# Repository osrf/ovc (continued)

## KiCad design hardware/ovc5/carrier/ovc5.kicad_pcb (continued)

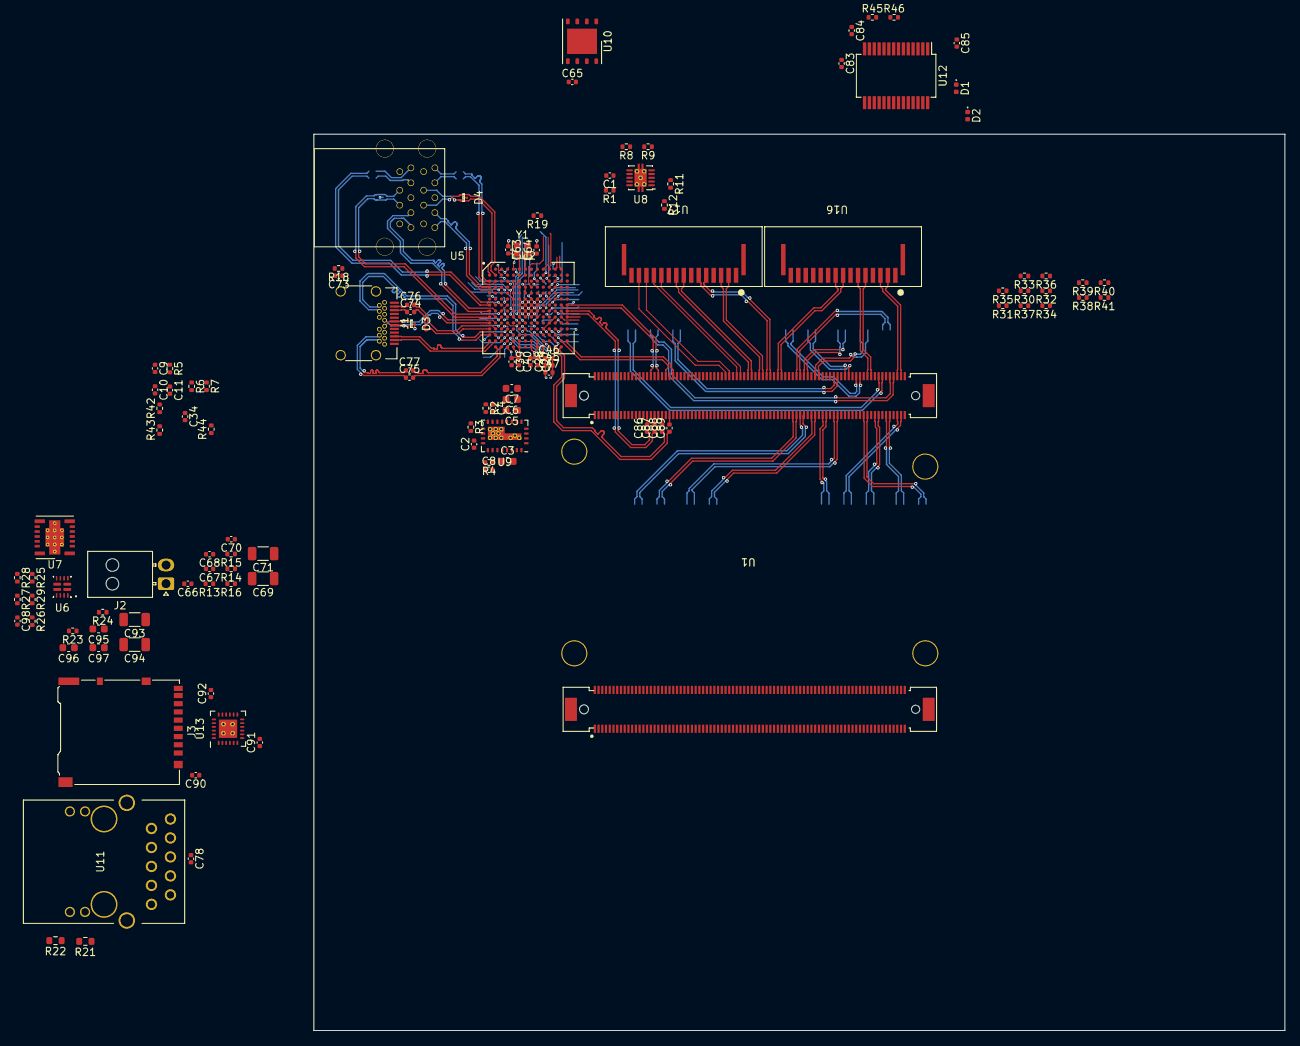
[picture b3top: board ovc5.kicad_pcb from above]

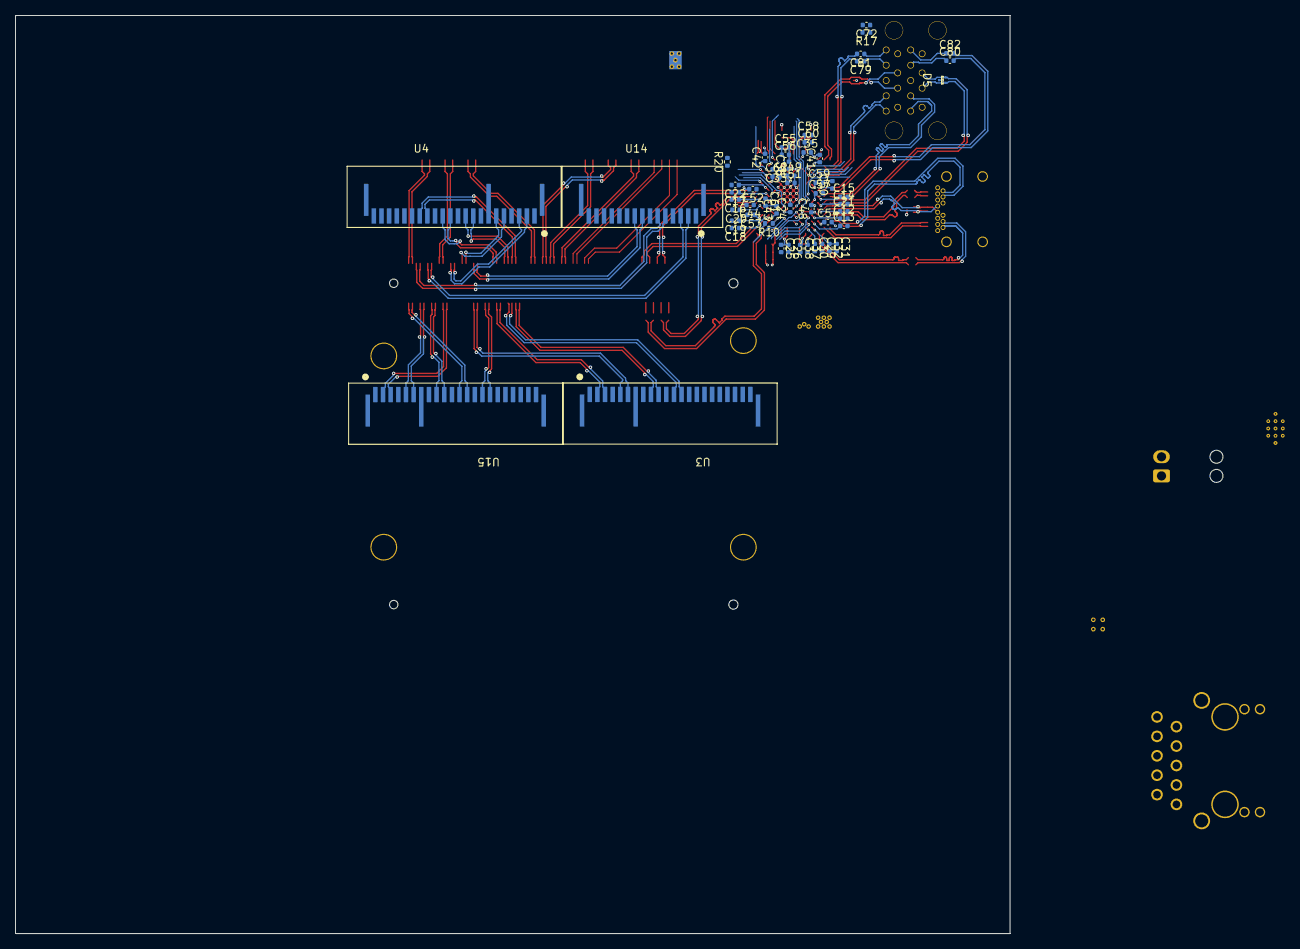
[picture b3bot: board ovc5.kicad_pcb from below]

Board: 6 copper layers, 130.0 x 120.0 mm, 169 parts (55 on the bottom side), 204 nets.

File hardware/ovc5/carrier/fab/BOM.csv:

Reference,Value,Footprint,D1N,D1PN,MFN,MPN,Quantity
"C25, C34, C47",10u,Capacitor_SMD:C_0402_1005Metric,Digikey,1276-6830-1-ND,Samsung,CL05A106MP8NUB8,3
"C2, C9, C33, C35, C55, C58, C90",1u,Capacitor_SMD:C_0402_1005Metric,Digikey,1276-1076-1-ND,Samsung,CL05A105KP5NNNC,7
"C1, C8, C10-C22, C24, C30, C32, C36-C45, C48-C50, C52-C54, C56, C57, C59-C61, C65-C68, C70, C74-C89, C91, C92, C98-C101",100n,Capacitor_SMD:C_0402_1005Metric,Digikey,1276-1043-1-ND,Samsung,CL05A104KA5NNNC,66
"C26-C28, C46, C51",10n,Capacitor_SMD:C_0402_1005Metric,Digikey,1276-1051-1-ND,Samsung,CL05B103KO5NNNC,5
"C29, C31, C62",4u7,Capacitor_SMD:C_0402_1005Metric,Digikey,587-3408-1-ND,Taiyo Yuden,LMK105BBJ475MVLF,3
"C4, C63, C64",10p,Capacitor_SMD:C_0402_1005Metric,Digikey,587-1947-1-ND,Taiyo Yuden,UMK105CG100DV-F,3
"C69, C71",150u,Capacitor_SMD:C_Elec_6.3x7.7,Digikey,PCE4401CT-ND,TDK,EEE-FKC151XAP,2
"C3, C5-C7, C23, C72, C73, C95-C97",22u,Capacitor_SMD:C_0603_1608Metric,Digikey,1276-6504-1-ND,Samsung,CL10A226MPCNUBE,10
"C93, C94",10u,Capacitor_SMD:C_1206_3216Metric,Digikey,1276-2876-1-ND,Samsung,CL31A106KBHNNNE,2
"C102, C103",2n2,Capacitor_SMD:C_0402_1005Metric,Digikey,1276-1532-1-ND,Samsung,CL05B222JB5NNNC,2
"CONN1, CONN2",Conn_Dummy,,Digikey,H122323-ND,Hirose,FX10A-168P-SV(71),2
D3-D5,D_TVS_Dual_AAC,USB:TPD2EUSB30x,Digikey,296-25509-1-ND,TI,TPD2EUSB30DRTR,3
"D2, D6",LED_Small,LED_SMD:LED_0402_1005Metric,Digikey,475-3112-1-ND,OSRAM,LB QH9G-N1OO-35-1,2
D7,LED_Small,LED_SMD:LED_0402_1005Metric,Digikey,475-3429-1-ND,OSRAM,LR VH9F-P2R1-1-Z,1
"D1, D8",LED_Small,LED_SMD:LED_0402_1005Metric,Digikey,475-3445-1-ND,OSRAM,LT VH9G-Q2OO-25-1,2
"FB1, FB2",MH2029-100Y,Inductor_SMD:L_0805_2012Metric,Digikey,MH2029-100YCT-ND,Bourns,MH2029-100Y,2
J1,USB_C_Receptacle,USB:USB_C_Receptacle_Wurth_632723300011,Digikey,732-9618-1-ND,Wurth,632723300011,1
J2,AUX_PWR,Connector_BarrelJack:BarrelJack_CUI_PJ-102AH_Horizontal,Digikey,CP-102AH-ND,CUI Devices,PJ-102AH,1
J3,Micro_SD_Card_Det_Hirose_DM3AT,Connector_Card:microSD_HC_Hirose_DM3AT-SF-PEJM5,RS-Online,828-1884,Hirose,DM3AT-SF-PEJM5,1
J4,JTAG,Connector_PinHeader_2.54mm:PinHeader_2x03_P2.54mm_Vertical,Digikey,1849-PR20203VBDN-ND,METZ Connect,PR20203VBDN,1
"J5, J7, J8",Conn_01x04,Connector_JST:JST_SH_BM04B-SRSS-TB_1x04-1MP_P1.00mm_Vertical,Digikey,455-1790-1-ND,JST,BM04B-SRSS-TB(LF)(SN),3
J9,Conn_01x04,Connector_Molex:Molex_SL_171971-0004_1x04_P2.54mm_Vertical,Digikey,WM22646-ND,Molex,1719710004,1
J10,Conn_01x02,Batteries_OSRF:ELNA_DSK-3R3H224U-HL,Digikey,604-1020-1-ND,Elna,DSK-3R3H224U-HL,1
"R1, R4, R25, R27",47k,Resistor_SMD:R_0402_1005Metric,Digikey,311-47.0KLRCT-ND,Yageo,RC0402FR-0747KL,4
"R2, R3",348k,Resistor_SMD:R_0402_1005Metric,Digikey,2019-RK73H1ETTP3483FCT-ND,KOA Speer,RK73H1ETTP3483F,2
"R5, R10, R29",20k,Resistor_SMD:R_0402_1005Metric,Digikey,311-20.0KLRCT-ND,Yageo,RC0402FR-0720KL,3
"R14, R16",1k,Resistor_SMD:R_0402_1005Metric,Digikey,RR05P1.0KDCT-ND,Susumu,RR0510P-102-D,2
"R19, R20",5k1,Resistor_SMD:R_0402_1005Metric,Digikey,RR05P5.1KDCT-ND,Susumu,RR0510P-512-D,2
"R21, R22",110R,Resistor_SMD:R_0603_1608Metric,Digikey,P110JCT-ND,Panasonic,ERJ-2GEJ111X,2
"R18, R24, R30-R43, R47-R51",2k4,Resistor_SMD:R_0402_1005Metric,Digikey,P2.4KDECT-ND,Panasonic,ERA-2AED242X,21
"R45, R46, R53-R55",220R,Resistor_SMD:R_0402_1005Metric,Digikey,541-10394-1-ND,Vishay Dale,RCS0402220RFKED,5
R57,1M,Resistor_SMD:R_0402_1005Metric,Digikey,P1.00MLCT-ND,Panasonic,ERJ-2RKF1004X,1
"R8, R9, R11, R12, R58, R59",100k,Resistor_SMD:R_0402_1005Metric,Digikey,YAG3515CT-ND,Yageo,YAG3515CT-ND,6
"R6, R7, R13, R15, R17, R23, R26, R28, R44, R52, R56, R60",10k,Resistor_SMD:R_0402_1005Metric,Digikey,YAG3436CT-ND,Yageo,AC0402FR-0710KL,12
SW1,SW_DIP_x03,Button_Switch_SMD:SW_DIP_SPSTx03_Slide_6.7x9.18mm_W6.73mm_P2.54mm_LowProfile_JPin,Digikey,CT2193MST-ND,CTS,219-3MST,1
U2,CYUSB43x7,USB:BGA-192_14x14_12.0x12.0mm,Arrow,CYUSB4347-BZXCES ,Cypress,CYUSB4347-BZXCES ,1
U5,USB3_A_Dual_Stacked,Connectors_OSRF:USB3_A_Dual_Stacked,Digikey,WM10420-ND,Molex,484060003,1
U6,TPS2121,TI:Texas_VQFN-HR-12_2x2.5_Pitch0.5mm,Digikey,296-53410-1-ND,TI,TPS2121RUXR,1
U7,TPSM53604RDA,Package_DFN_QFN:Texas_B3QFN-14-1EP_5x5.5mm_P0.65mm_ThermalVia,Digikey,296-TPSM53604RDARCT-ND,TI,TPSM53604RDAR,1
U8,TPS2561,Package_SON:VSON-10-1EP_3x3mm_P0.5mm_EP1.65x2.4mm_ThermalVias,Digikey,296-37670-1-ND,TI,TPS2561DRCR,1
U9,EN5339QI,DCDC:Converter_DCDC_Intel_QFN-24_4x6mm_P0.65mm_ThermalVias,Digikey,544-2854-1-ND,Intel,EN5339QI,1
U10,S25FL064,Package_SON:WSON-8-1EP_6x5mm_P1.27mm_EP3.4x4mm,Digikey,428-4640-1-ND,Cypress,S25FL064LABNFI013,1
U11,ARJ11C-MBSAS-A-BA-7MU2,Ethernet:ARJ11C-MBSAS-A-BA-7MU2,Digikey,ARJ11C-MBSAS-A-BA-7MU2-ND,Abracon,ARJ11C-MBSAS-A-BA-7MU2,1
U12,FT232RL,Package_SO:SSOP-28_5.3x10.2mm_P0.65mm,Digikey,768-1306-ND,FTDI,FT232RL-TUBE,1
U13,TXS02612,WQFN:TI_RTW0024B,Digikey,296-23869-1-ND,TI,TXS02612RTWR,1
"U3, U4, U15",PICAM_Expandable,Connectors_OSRF:AMPHENOL_SFW22S,Digikey,609-1158-1-ND,Amphenol,SFW22S-2STE1LF,3
"U14, U16, U17",PICAM,Connectors_OSRF:AMPHENOL_SFW15S,Digikey,609-1148-1-ND,Amphenol,SFW15S-2STE1LF,3
U18,74LVC2T45DC,Package_SO:VSSOP-8_2.3x2mm_P0.5mm,Digikey,1727-4578-1-ND,Nexperia,"74LVC2T45DC,125",1
Y1,25MHz,Crystal:Crystal_SMD_2016-4Pin_2.0x1.6mm,Digikey,535-13851-1-ND,Abracon,ABM11W-25.0000MHZ-7-K1Z-T3,1

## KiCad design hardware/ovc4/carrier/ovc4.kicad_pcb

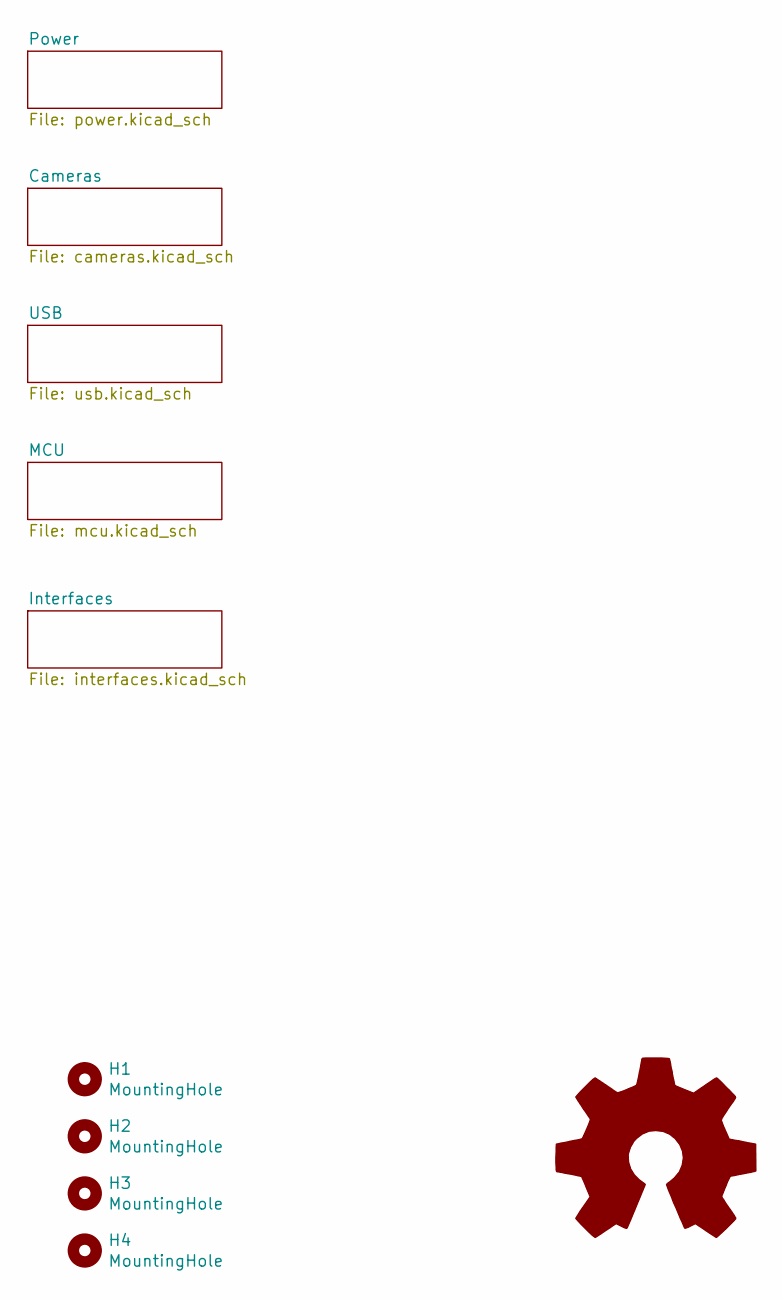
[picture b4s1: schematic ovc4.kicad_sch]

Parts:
H1, H2, H3, H4: MountingHole; MountingHole_2.5mm
LOGO1: Logo_Open_Hardware_Large; OSHW-Logo2_7.3x6mm_SilkScreen

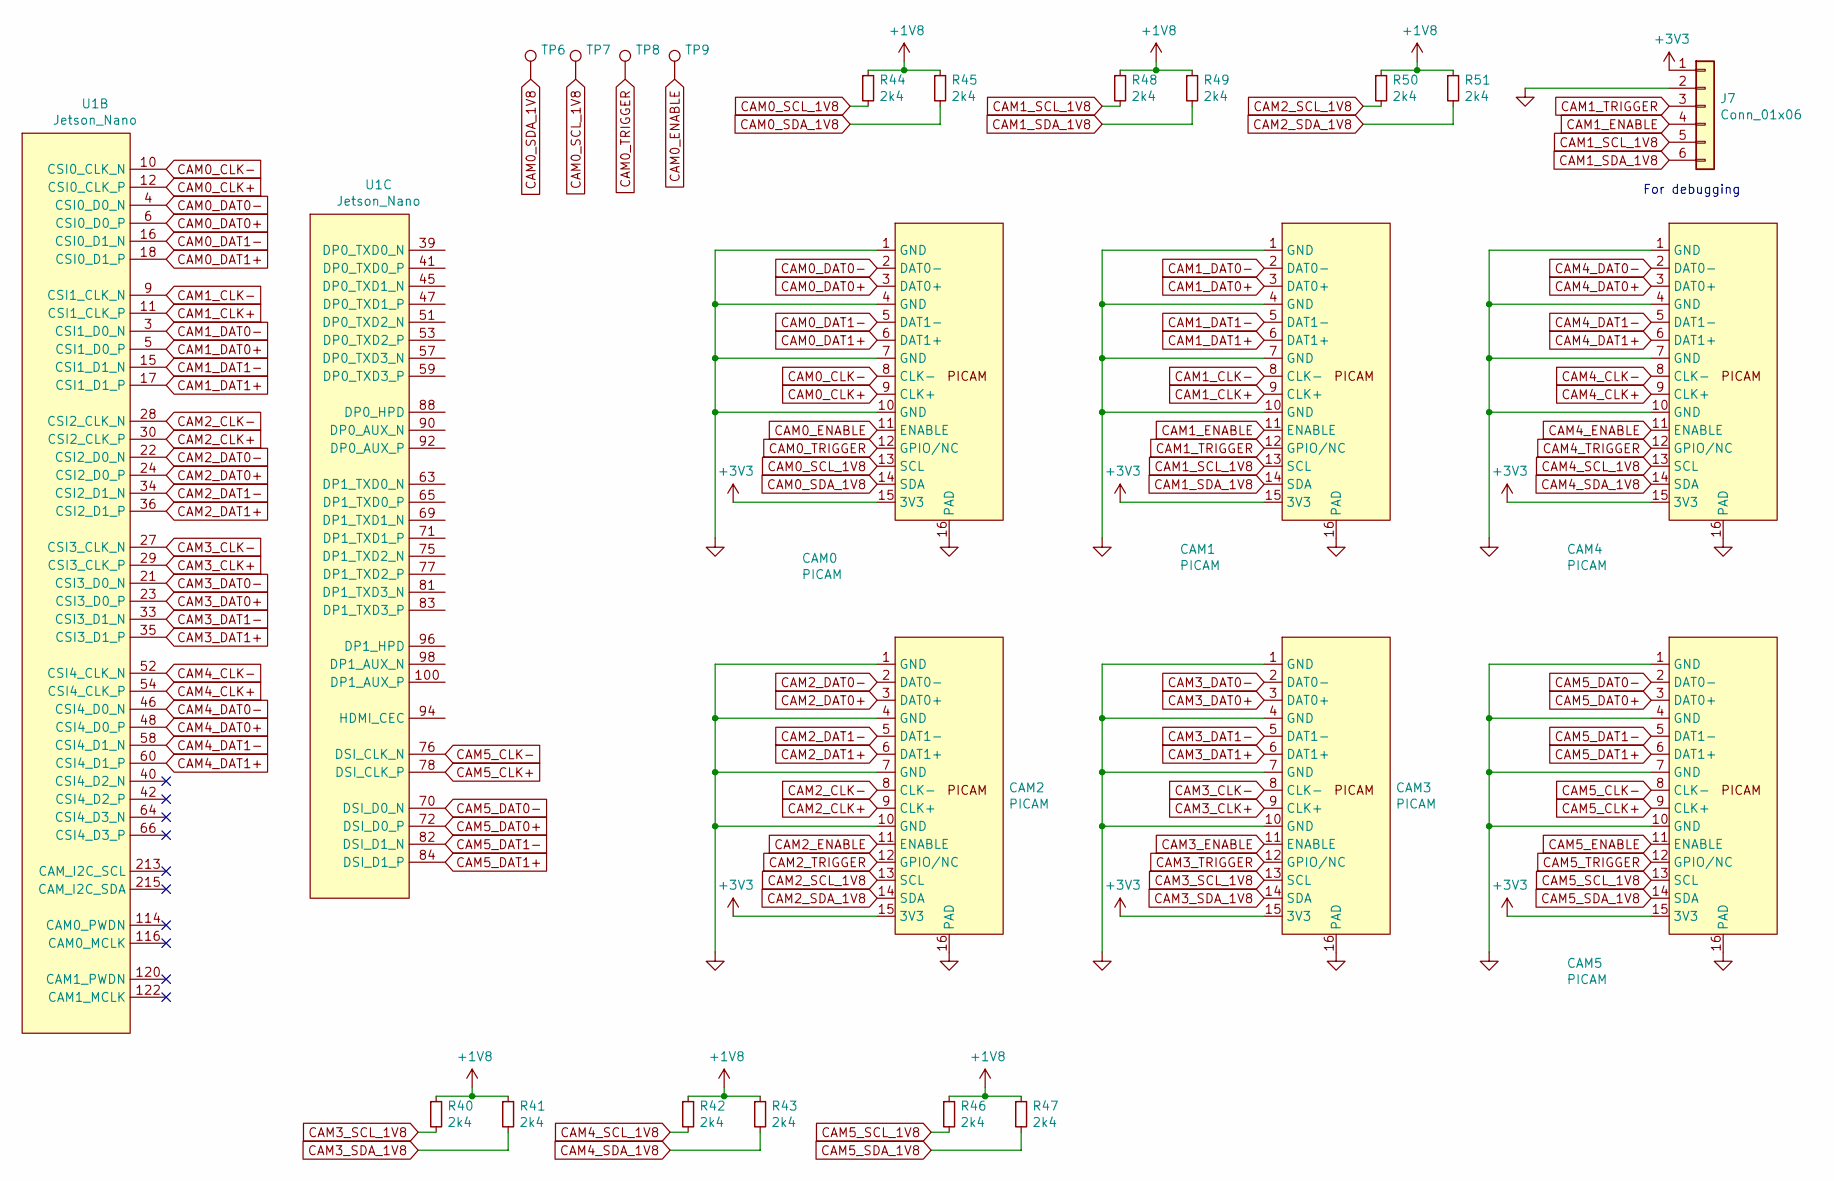
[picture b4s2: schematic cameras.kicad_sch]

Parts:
CAM0, CAM1, CAM2, CAM3, CAM4, CAM5: PICAM; AMPHENOL_SFW15R; MPN SFW15R-1STE1LF
J7: Conn_01x06; PinHeader_1x06_P2.54mm_Vertical; MPN 68000-406HLF
R40, R41, R42, R43, R44, R45, R46, R47, R48, R49, R50, R51: 2k4; R_0402_1005Metric; MPN ERA-2AED242X
TP6, TP7, TP8, TP9: Testpoint; TestPoint_Pad_D1.0mm
U1: Jetson_Nano; TE_2309413-1; MPN 2309413-1

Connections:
+1V8: R40.1, R41.1, R42.1, R43.1, R44.1, R45.1, R46.1, R47.1, R48.1, R49.1, R50.1, R51.1; also elsewhere on the board
CAM0_CLK+: CAM0.9 (CLK+), U1.12 (CSI0_CLK_P)
CAM0_CLK-: CAM0.8 (CLK-), U1.10 (CSI0_CLK_N)
CAM0_DAT0+: CAM0.3 (DAT0+), U1.6 (CSI0_D0_P)
CAM0_DAT0-: CAM0.2 (DAT0-), U1.4 (CSI0_D0_N)
CAM0_DAT1+: CAM0.6 (DAT1+), U1.18 (CSI0_D1_P)
CAM0_DAT1-: CAM0.5 (DAT1-), U1.16 (CSI0_D1_N)
CAM0_ENABLE: CAM0.11 (ENABLE), TP9.1; also elsewhere on the board
CAM0_SCL_1V8: CAM0.13 (SCL), R44.2, TP7.1; also elsewhere on the board
CAM0_SDA_1V8: CAM0.14 (SDA), R45.2, TP6.1; also elsewhere on the board
CAM0_TRIGGER: CAM0.12 (GPIO/NC), TP8.1; also elsewhere on the board
CAM1_CLK+: CAM1.9 (CLK+), U1.11 (CSI1_CLK_P)
CAM1_CLK-: CAM1.8 (CLK-), U1.9 (CSI1_CLK_N)
CAM1_DAT0+: CAM1.3 (DAT0+), U1.5 (CSI1_D0_P)
CAM1_DAT0-: CAM1.2 (DAT0-), U1.3 (CSI1_D0_N)
CAM1_DAT1+: CAM1.6 (DAT1+), U1.17 (CSI1_D1_P)
CAM1_DAT1-: CAM1.5 (DAT1-), U1.15 (CSI1_D1_N)
CAM1_ENABLE: CAM1.11 (ENABLE), J7.4; also elsewhere on the board
CAM1_SCL_1V8: CAM1.13 (SCL), J7.5, R48.2; also elsewhere on the board
CAM1_SDA_1V8: CAM1.14 (SDA), J7.6, R49.2; also elsewhere on the board
CAM1_TRIGGER: CAM1.12 (GPIO/NC), J7.3; also elsewhere on the board
CAM2_CLK+: CAM2.9 (CLK+), U1.30 (CSI2_CLK_P)
CAM2_CLK-: CAM2.8 (CLK-), U1.28 (CSI2_CLK_N)
CAM2_DAT0+: CAM2.3 (DAT0+), U1.24 (CSI2_D0_P)
CAM2_DAT0-: CAM2.2 (DAT0-), U1.22 (CSI2_D0_N)
CAM2_DAT1+: CAM2.6 (DAT1+), U1.36 (CSI2_D1_P)
CAM2_DAT1-: CAM2.5 (DAT1-), U1.34 (CSI2_D1_N)
CAM2_ENABLE: CAM2.11 (ENABLE); also elsewhere on the board
CAM2_SCL_1V8: CAM2.13 (SCL), R50.2; also elsewhere on the board
CAM2_SDA_1V8: CAM2.14 (SDA), R51.2; also elsewhere on the board
CAM2_TRIGGER: CAM2.12 (GPIO/NC); also elsewhere on the board
CAM3_CLK+: CAM3.9 (CLK+), U1.29 (CSI3_CLK_P)
CAM3_CLK-: CAM3.8 (CLK-), U1.27 (CSI3_CLK_N)
CAM3_DAT0+: CAM3.3 (DAT0+), U1.23 (CSI3_D0_P)
CAM3_DAT0-: CAM3.2 (DAT0-), U1.21 (CSI3_D0_N)
CAM3_DAT1+: CAM3.6 (DAT1+), U1.35 (CSI3_D1_P)
CAM3_DAT1-: CAM3.5 (DAT1-), U1.33 (CSI3_D1_N)
CAM3_ENABLE: CAM3.11 (ENABLE); also elsewhere on the board
CAM3_SCL_1V8: CAM3.13 (SCL), R40.2; also elsewhere on the board
CAM3_SDA_1V8: CAM3.14 (SDA), R41.2; also elsewhere on the board
CAM3_TRIGGER: CAM3.12 (GPIO/NC); also elsewhere on the board
CAM4_CLK+: CAM4.9 (CLK+), U1.54 (CSI4_CLK_P)
CAM4_CLK-: CAM4.8 (CLK-), U1.52 (CSI4_CLK_N)
CAM4_DAT0+: CAM4.3 (DAT0+), U1.48 (CSI4_D0_P)
CAM4_DAT0-: CAM4.2 (DAT0-), U1.46 (CSI4_D0_N)
CAM4_DAT1+: CAM4.6 (DAT1+), U1.60 (CSI4_D1_P)
CAM4_DAT1-: CAM4.5 (DAT1-), U1.58 (CSI4_D1_N)
CAM4_ENABLE: CAM4.11 (ENABLE); also elsewhere on the board
CAM4_SCL_1V8: CAM4.13 (SCL), R42.2; also elsewhere on the board
CAM4_SDA_1V8: CAM4.14 (SDA), R43.2; also elsewhere on the board
CAM4_TRIGGER: CAM4.12 (GPIO/NC); also elsewhere on the board
CAM5_CLK+: CAM5.9 (CLK+), U1.78 (DSI_CLK_P)
CAM5_CLK-: CAM5.8 (CLK-), U1.76 (DSI_CLK_N)
CAM5_DAT0+: CAM5.3 (DAT0+), U1.72 (DSI_D0_P)
CAM5_DAT0-: CAM5.2 (DAT0-), U1.70 (DSI_D0_N)
CAM5_DAT1+: CAM5.6 (DAT1+), U1.84 (DSI_D1_P)
CAM5_DAT1-: CAM5.5 (DAT1-), U1.82 (DSI_D1_N)
CAM5_ENABLE: CAM5.11 (ENABLE); also elsewhere on the board
CAM5_SCL_1V8: CAM5.13 (SCL), R46.2; also elsewhere on the board
CAM5_SDA_1V8: CAM5.14 (SDA), R47.2; also elsewhere on the board
CAM5_TRIGGER: CAM5.12 (GPIO/NC); also elsewhere on the board
GND: CAM0.1 (GND), CAM0.4 (GND), CAM0.7 (GND), CAM0.10 (GND), CAM0.16 (PAD), CAM1.1 (GND), CAM1.4 (GND), CAM1.7 (GND), CAM1.10 (GND), CAM1.16 (PAD), CAM2.1 (GND), CAM2.4 (GND), CAM2.7 (GND), CAM2.10 (GND), CAM2.16 (PAD), CAM3.1 (GND), CAM3.4 (GND), CAM3.7 (GND), CAM3.10 (GND), CAM3.16 (PAD), CAM4.1 (GND), CAM4.4 (GND), CAM4.7 (GND), CAM4.10 (GND), CAM4.16 (PAD), CAM5.1 (GND), CAM5.4 (GND), CAM5.7 (GND), CAM5.10 (GND), CAM5.16 (PAD), J7.2; also elsewhere on the board

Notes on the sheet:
For debugging

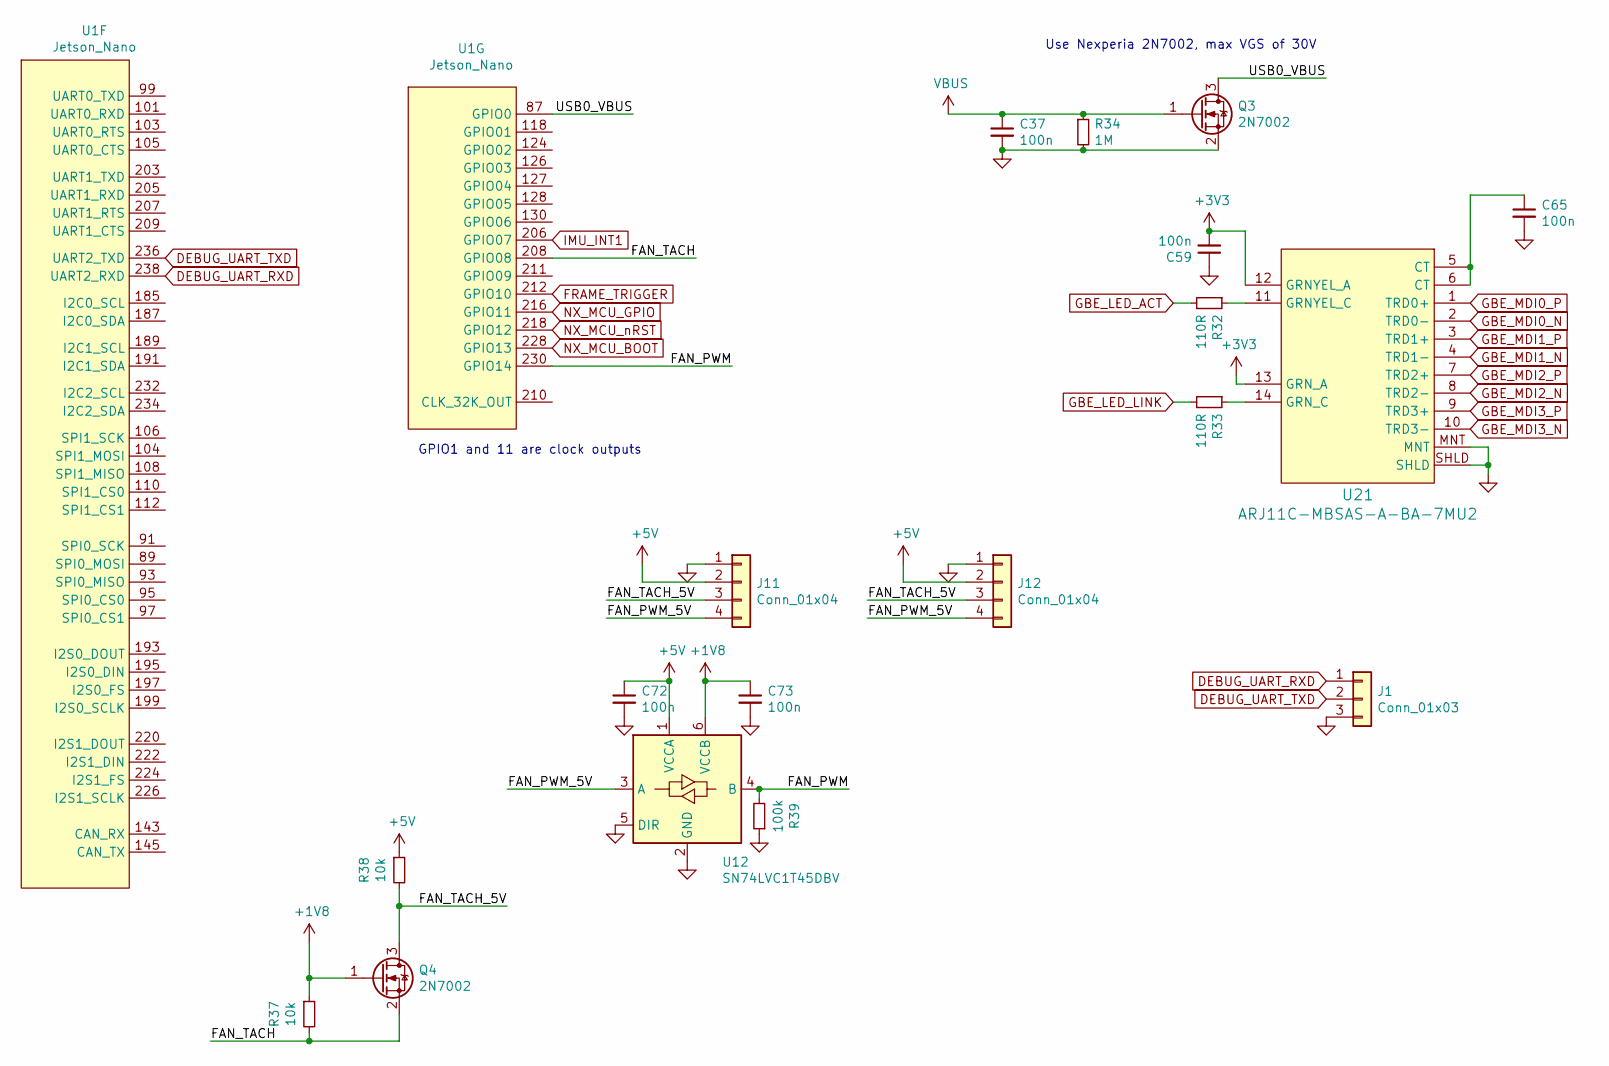
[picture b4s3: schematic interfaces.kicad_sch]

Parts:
C37, C59, C65, C72, C73: 100n; C_0402_1005Metric; MPN CL05F104ZO5NNNC
J1: Conn_01x03; PinHeader_1x03_P2.54mm_Vertical; MPN CONN HEADER VERT 3POS 2.54MM
J11: Conn_01x04; PinHeader_1x04_P1.27mm_Vertical; MPN HPH1-B-04-UA
J12: Conn_01x04; PinHeader_1x04_P2.54mm_Vertical; MPN 61300411121
Q3, Q4: 2N7002; SOT-23; MPN 2N7002,215
R32, R33: 110R; R_0603_1608Metric; MPN ERA-3AEB111V
R34: 1M; R_0402_1005Metric; MPN RC0402FR-071ML
R37, R38: 10k; R_0402_1005Metric; MPN ERA-2AED103X
R39: 100k; R_0402_1005Metric; MPN ERA-2AED104X
U1: Jetson_Nano; TE_2309413-1; MPN 2309413-1
U12: SN74LVC1T45DBV; SOT-23-6; MPN SN74LVC1T45DBVR
U21: ARJ11C-MBSAS-A-BA-7MU2; MPN ARJ11C-MBSAS-A-BA-7MU2

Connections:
+1V8: C73.1, Q4.1 (G), R37.1, U12.6 (VCCB); also elsewhere on the board
+5V: C72.1, J11.2, J12.2, R38.1, U12.1 (VCCA); also elsewhere on the board
/Interfaces/FAN_PWM: R39.2, U1.230 (GPIO14), U12.4 (B)
/Interfaces/FAN_PWM_5V: J11.4, J12.4, U12.3 (A)
/Interfaces/FAN_TACH: Q4.2 (S), R37.2, U1.208 (GPIO08)
/Interfaces/FAN_TACH_5V: J11.3, J12.3, Q4.3 (D), R38.2
/Interfaces/USB0_VBUS: Q3.3 (D), U1.87 (GPIO0)
DEBUG_UART_RXD: J1.1, U1.238 (UART2_RXD)
DEBUG_UART_TXD: J1.2, U1.236 (UART2_TXD)
FRAME_TRIGGER: U1.212 (GPIO10); also elsewhere on the board
GBE_LED_ACT: R32.2; also elsewhere on the board
GBE_LED_LINK: R33.2; also elsewhere on the board
GBE_MDI0_N: U21.2 (TRD0-); also elsewhere on the board
GBE_MDI0_P: U21.1 (TRD0+); also elsewhere on the board
GBE_MDI1_N: U21.4 (TRD1-); also elsewhere on the board
GBE_MDI1_P: U21.3 (TRD1+); also elsewhere on the board
GBE_MDI2_N: U21.8 (TRD2-); also elsewhere on the board
GBE_MDI2_P: U21.7 (TRD2+); also elsewhere on the board
GBE_MDI3_N: U21.10 (TRD3-); also elsewhere on the board
GBE_MDI3_P: U21.9 (TRD3+); also elsewhere on the board
GND: C37.2, C59.1, C65.2, C72.2, C73.2, J1.3, J11.1, J12.1, Q3.2 (S), R34.2, R39.1, U12.2 (GND), U12.5 (DIR), U21.MNT, U21.SHLD; also elsewhere on the board
IMU_INT1: U1.206 (GPIO07); also elsewhere on the board
NX_MCU_BOOT: U1.228 (GPIO13); also elsewhere on the board
NX_MCU_GPIO: U1.216 (GPIO11); also elsewhere on the board
NX_MCU_nRST: U1.218 (GPIO12); also elsewhere on the board
unnamed: C65.1, U21.5 (CT), U21.6 (CT)
unnamed: R32.1, U21.11 (GRNYEL_C)
unnamed: R33.1, U21.14 (GRN_C)
VBUS: C37.1, Q3.1 (G), R34.1; also elsewhere on the board

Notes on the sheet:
GPIO1 and 11 are clock outputs
Use Nexperia 2N7002, max VGS of 30V

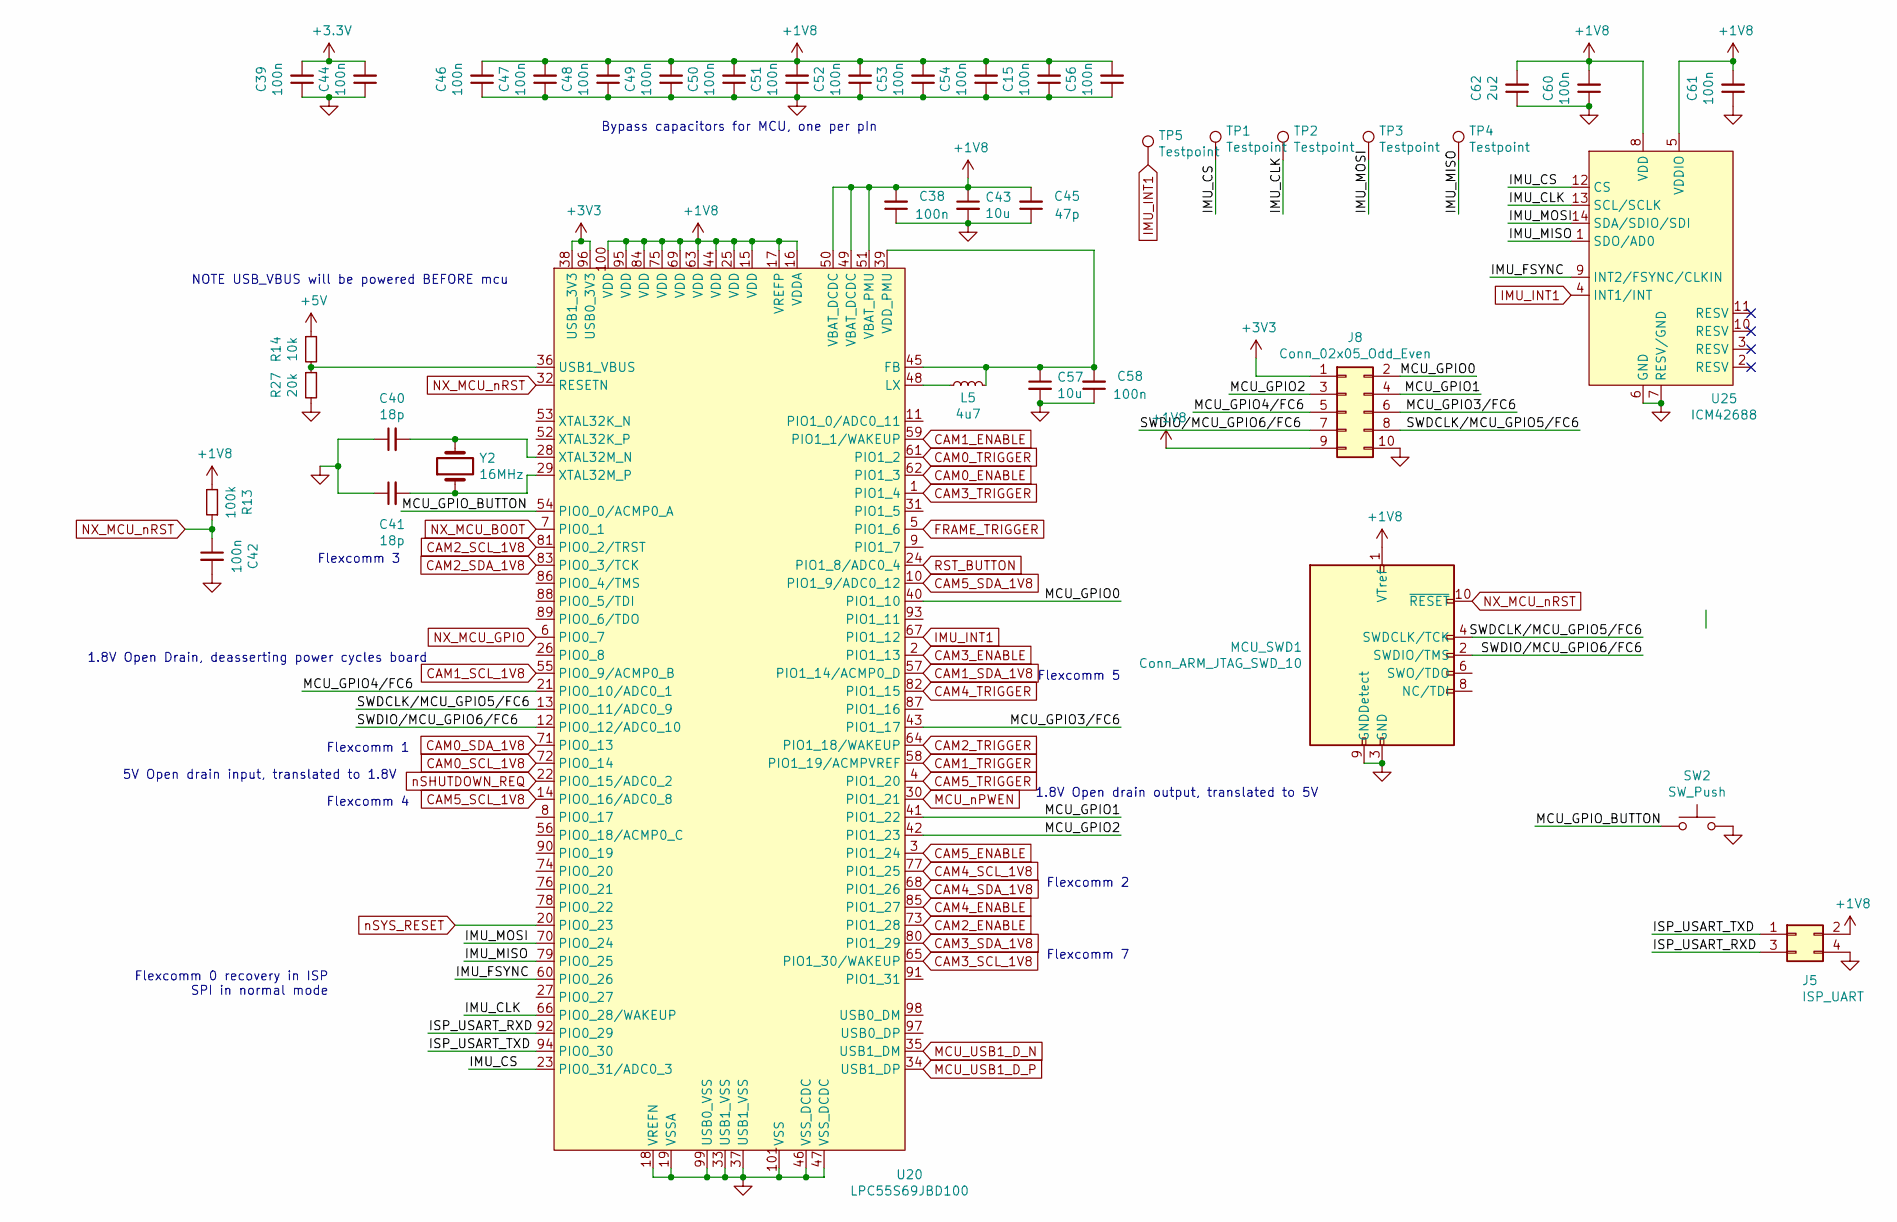
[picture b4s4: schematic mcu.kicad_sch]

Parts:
C15, C38, C39, C42, C44, C46, C47, C48, C49, C50, C51, C52, C53, C54, C56, C58, C60, C61: 100n; C_0402_1005Metric; MPN CL05F104ZO5NNNC
C40, C41: 18p; C_0402_1005Metric; MPN CC0402JRNPO9BN180
C43, C57: 10u; C_0603_1608Metric; MPN GRM188R61A106KE69J
C45: 47p; C_0402_1005Metric; MPN C0402C470K5GACTU
C62: 2u2; C_0402_1005Metric; MPN GRM155R61A225KE95D
J5: ISP_UART; PinHeader_2x02_P2.54mm_Vertical; MPN M20-9760246
J8: Conn_02x05_Odd_Even; PinHeader_2x05_P2.54mm_Vertical; MPN PPTC052LFBN-RC
L5: 4u7; L_0805_2012Metric; MPN LQM2MPN4R7MG0L
MCU_SWD1: Conn_ARM_JTAG_SWD_10; PinHeader_2x05_P1.27mm_Vertical; MPN 20021111-00010T4LF
R13: 100k; R_0402_1005Metric; MPN ERA-2AED104X
R14: 10k; R_0402_1005Metric; MPN ERA-2AED103X
R27: 20k; R_0402_1005Metric; MPN ERA-2AED103X
SW2: SW_Push; SW_PUSH_6mm_H5mm; MPN 1825910-7
TP1, TP2, TP3, TP4, TP5: Testpoint; TestPoint_Pad_D1.0mm
U20: LPC55S69JBD100; QFP-100-1EP_3.21x3.21mm_14x14_Pitch0.5mm; MPN LPC55S69JBD100K
U25: ICM42688; LGA-14_3x2.5mm_P0.5mm_LayoutBorder3x4y; MPN ICM-42688-P
Y2: 16MHz; Crystal_SMD_5032-2Pin_5.0x3.2mm; MPN CX5032GB16000H0PESZZ

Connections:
+1V8: C15.2, C38.2, C43.1, C45.2, C46.2, C47.2, C48.2, C49.2, C50.2, C51.2, C52.2, C53.2, C54.2, C56.2, C60.2, C61.2, C62.2, J5.2, J8.9, MCU_SWD1.1 (VTref), R13.2, U20.15 (VDD), U20.16 (VDDA), U20.17 (VREFP), U20.25 (VDD), U20.44 (VDD), U20.49 (VBAT_DCDC), U20.50 (VBAT_DCDC), U20.51 (VBAT_PMU), U20.63 (VDD), U20.69 (VDD), U20.75 (VDD), U20.84 (VDD), U20.95 (VDD), U20.100 (VDD), U25.5 (VDDIO), U25.8 (VDD); also elsewhere on the board
+5V: R14.1; also elsewhere on the board
/MCU/IMU_CLK: TP2.1, U20.66 (PIO0_28/WAKEUP), U25.13 (SCL/SCLK)
/MCU/IMU_CS: TP1.1, U20.23 (PIO0_31/ADC0_3), U25.12 (CS)
/MCU/IMU_FSYNC: U20.60 (PIO0_26), U25.9 (INT2/FSYNC/CLKIN)
/MCU/IMU_MISO: TP4.1, U20.79 (PIO0_25), U25.1 (SDO/AD0)
/MCU/IMU_MOSI: TP3.1, U20.70 (PIO0_24), U25.14 (SDA/SDIO/SDI)
/MCU/ISP_USART_RXD: J5.3, U20.92 (PIO0_29)
/MCU/ISP_USART_TXD: J5.1, U20.94 (PIO0_30)
/MCU/MCU_GPIO0: J8.2, U20.40 (PIO1_10)
/MCU/MCU_GPIO1: J8.4, U20.41 (PIO1_22)
/MCU/MCU_GPIO2: J8.3, U20.42 (PIO1_23)
/MCU/MCU_GPIO3/FC6: J8.6, U20.43 (PIO1_17)
/MCU/MCU_GPIO4/FC6: J8.5, U20.21 (PIO0_10/ADC0_1)
/MCU/MCU_GPIO_BUTTON: SW2.1, U20.54 (PIO0_0/ACMP0_A)
/MCU/SWDCLK/MCU_GPIO5/FC6: J8.8, MCU_SWD1.4 (SWDCLK/TCK), U20.13 (PIO0_11/ADC0_9)
/MCU/SWDIO/MCU_GPIO6/FC6: J8.7, MCU_SWD1.2 (SWDIO/TMS), U20.12 (PIO0_12/ADC0_10)
CAM0_ENABLE: U20.62 (PIO1_3); also elsewhere on the board
CAM0_SCL_1V8: U20.72 (PIO0_14); also elsewhere on the board
CAM0_SDA_1V8: U20.71 (PIO0_13); also elsewhere on the board
CAM0_TRIGGER: U20.61 (PIO1_2); also elsewhere on the board
CAM1_ENABLE: U20.59 (PIO1_1/WAKEUP); also elsewhere on the board
CAM1_SCL_1V8: U20.55 (PIO0_9/ACMP0_B); also elsewhere on the board
CAM1_SDA_1V8: U20.57 (PIO1_14/ACMP0_D); also elsewhere on the board
CAM1_TRIGGER: U20.58 (PIO1_19/ACMPVREF); also elsewhere on the board
CAM2_ENABLE: U20.73 (PIO1_28); also elsewhere on the board
CAM2_SCL_1V8: U20.81 (PIO0_2/TRST); also elsewhere on the board
CAM2_SDA_1V8: U20.83 (PIO0_3/TCK); also elsewhere on the board
CAM2_TRIGGER: U20.64 (PIO1_18/WAKEUP); also elsewhere on the board
CAM3_ENABLE: U20.2 (PIO1_13); also elsewhere on the board
CAM3_SCL_1V8: U20.65 (PIO1_30/WAKEUP); also elsewhere on the board
CAM3_SDA_1V8: U20.80 (PIO1_29); also elsewhere on the board
CAM3_TRIGGER: U20.1 (PIO1_4); also elsewhere on the board
CAM4_ENABLE: U20.85 (PIO1_27); also elsewhere on the board
CAM4_SCL_1V8: U20.77 (PIO1_25); also elsewhere on the board
CAM4_SDA_1V8: U20.68 (PIO1_26); also elsewhere on the board
CAM4_TRIGGER: U20.82 (PIO1_15); also elsewhere on the board
CAM5_ENABLE: U20.3 (PIO1_24); also elsewhere on the board
CAM5_SCL_1V8: U20.14 (PIO0_16/ADC0_8); also elsewhere on the board
CAM5_SDA_1V8: U20.10 (PIO1_9/ADC0_12); also elsewhere on the board
CAM5_TRIGGER: U20.4 (PIO1_20); also elsewhere on the board
FRAME_TRIGGER: U20.5 (PIO1_6); also elsewhere on the board
GND: C15.1, C38.1, C39.1, C40.1, C41.1, C42.2, C43.2, C44.1, C45.1, C46.1, C47.1, C48.1, C49.1, C50.1, C51.1, C52.1, C53.1, C54.1, C56.1, C57.2, C58.1, C60.1, C61.1, C62.1, J5.4, J8.10, MCU_SWD1.3 (GND), MCU_SWD1.5 (GND), MCU_SWD1.9 (GNDDetect), R27.2, SW2.2, U20.18 (VREFN), U20.19 (VSSA), U20.33 (USB1_VSS), U20.37 (USB1_VSS), U20.46 (VSS_DCDC), U20.47 (VSS_DCDC), U20.99 (USB0_VSS), U20.101 (VSS), U25.6 (GND), U25.7 (RESV/GND); also elsewhere on the board
IMU_INT1: TP5.1, U20.67 (PIO1_12), U25.4 (INT1/INT); also elsewhere on the board
MCU_USB1_D_N: U20.35 (USB1_DM); also elsewhere on the board
MCU_USB1_D_P: U20.34 (USB1_DP); also elsewhere on the board
MCU_nPWEN: U20.30 (PIO1_21); also elsewhere on the board
NX_MCU_BOOT: U20.7 (PIO0_1); also elsewhere on the board
NX_MCU_GPIO: U20.6 (PIO0_7); also elsewhere on the board
NX_MCU_nRST: C42.1, MCU_SWD1.10 (~RESET~), R13.1, U20.32 (RESETN); also elsewhere on the board
unnamed: C40.2, U20.28 (XTAL32M_N), Y2.2
unnamed: C41.2, U20.29 (XTAL32M_P), Y2.1
unnamed: C57.1, C58.2, L5.2, U20.39 (VDD_PMU), U20.45 (FB)
unnamed: L5.1, U20.48 (LX)
unnamed: R14.2, R27.1, U20.36 (USB1_VBUS)
RST_BUTTON: U20.24 (PIO1_8/ADC0_4); also elsewhere on the board
nSHUTDOWN_REQ: U20.22 (PIO0_15/ADC0_2); also elsewhere on the board
nSYS_RESET: U20.20 (PIO0_23); also elsewhere on the board

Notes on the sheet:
5V Open drain input, translated to 1.8V
Flexcomm 0 recovery in ISP SPI in normal mode
Flexcomm 3
Flexcomm 1
Flexcomm 4
1.8V Open Drain, deasserting power cycles board
NOTE USB_VBUS will be powered BEFORE mcu
Bypass capacitors for MCU, one per pIn
Flexcomm 5
Flexcomm 2
Flexcomm 7
1.8V Open drain output, translated to 5V
